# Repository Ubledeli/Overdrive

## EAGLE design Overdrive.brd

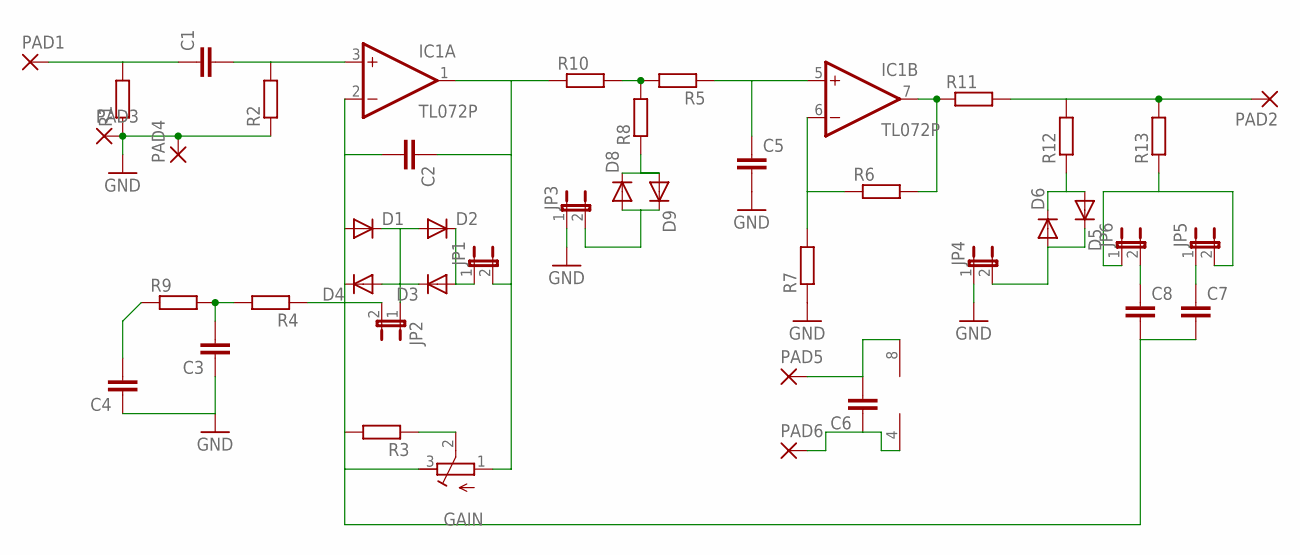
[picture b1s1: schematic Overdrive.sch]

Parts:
C1, C2, C3, C4, C5, C6, C7, C8: C-EU050-030X075; C050-030X075
D1, D2, D3, D4, D5, D6, D8, D9: 1N4148DO35-7; DO35-7
GAIN: R-TRIMM64W; RTRIM64W
IC1: TL072P; DIL08
JP1, JP2, JP3, JP4, JP5, JP6: JP1E; JP1
PAD1, PAD2, PAD3, PAD4, PAD5, PAD6: WIREPAD2,54/0,8; 2,54/0,8
R1, R2, R3, R4, R5, R6, R7, R8, R9, R10, R11, R12, R13: R-EU_0207/7; 0207/7

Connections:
GND: C3.1, C4.1, C5.2, JP3.1, JP4.1, PAD3.1, PAD4.1, R1.1, R2.1, R7.1
unnamed: C1.1, PAD1.1, R1.2
unnamed: C1.2, IC1.3 (+IN), R2.2
unnamed: C2.2, C7.2, C8.2, D1.A, D4.C, GAIN.3 (E), IC1.2 (-IN), JP2.2, R3.2, R4.1
unnamed: C2.1, GAIN.1 (A), IC1.1 (OUT), JP1.2, R10.1
unnamed: IC1.6 (-IN), R6.1, R7.2
unnamed: IC1.7 (OUT), R6.2, R11.1
unnamed: D1.C, D2.A, D3.C, D4.A, JP2.1
unnamed: D8.A, D9.C, JP3.2
unnamed: D2.C, D3.A, JP1.1
unnamed: GAIN.2 (S), R3.1
unnamed: C6.2, IC1.8 (V+), PAD5.1
unnamed: D8.C, D9.A, R8.1
unnamed: C4.2, R9.1
unnamed: C3.2, R4.2, R9.2
unnamed: R5.2, R8.2, R10.2
unnamed: C6.1, IC1.4 (V-), PAD6.1
unnamed: C5.1, IC1.5 (+IN), R5.1
unnamed: PAD2.1, R11.2, R12.2, R13.2
unnamed: D5.A, D6.C, R12.1
unnamed: D5.C, D6.A, JP4.2
unnamed: C8.1, JP6.2
unnamed: JP5.2, JP6.1, R13.1
unnamed: C7.1, JP5.1

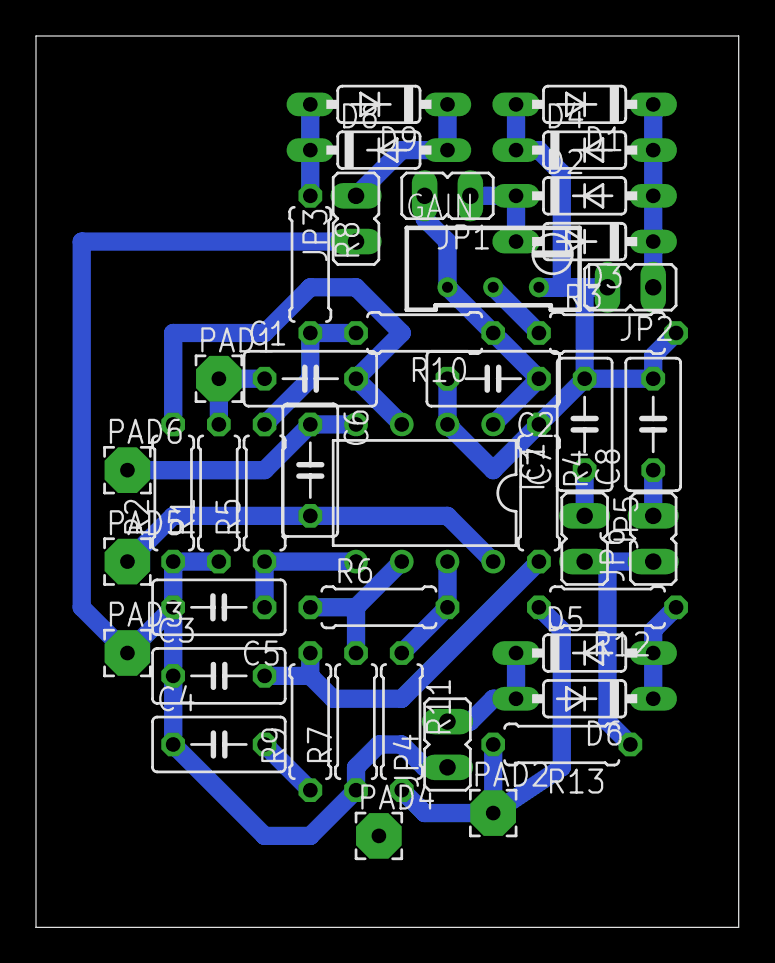
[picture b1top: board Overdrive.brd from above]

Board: 2 copper layers, 39.0 x 49.5 mm, 43 parts (0 on the bottom side), 24 nets.

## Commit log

2017-05-09 initial
2017-05-13 readme
